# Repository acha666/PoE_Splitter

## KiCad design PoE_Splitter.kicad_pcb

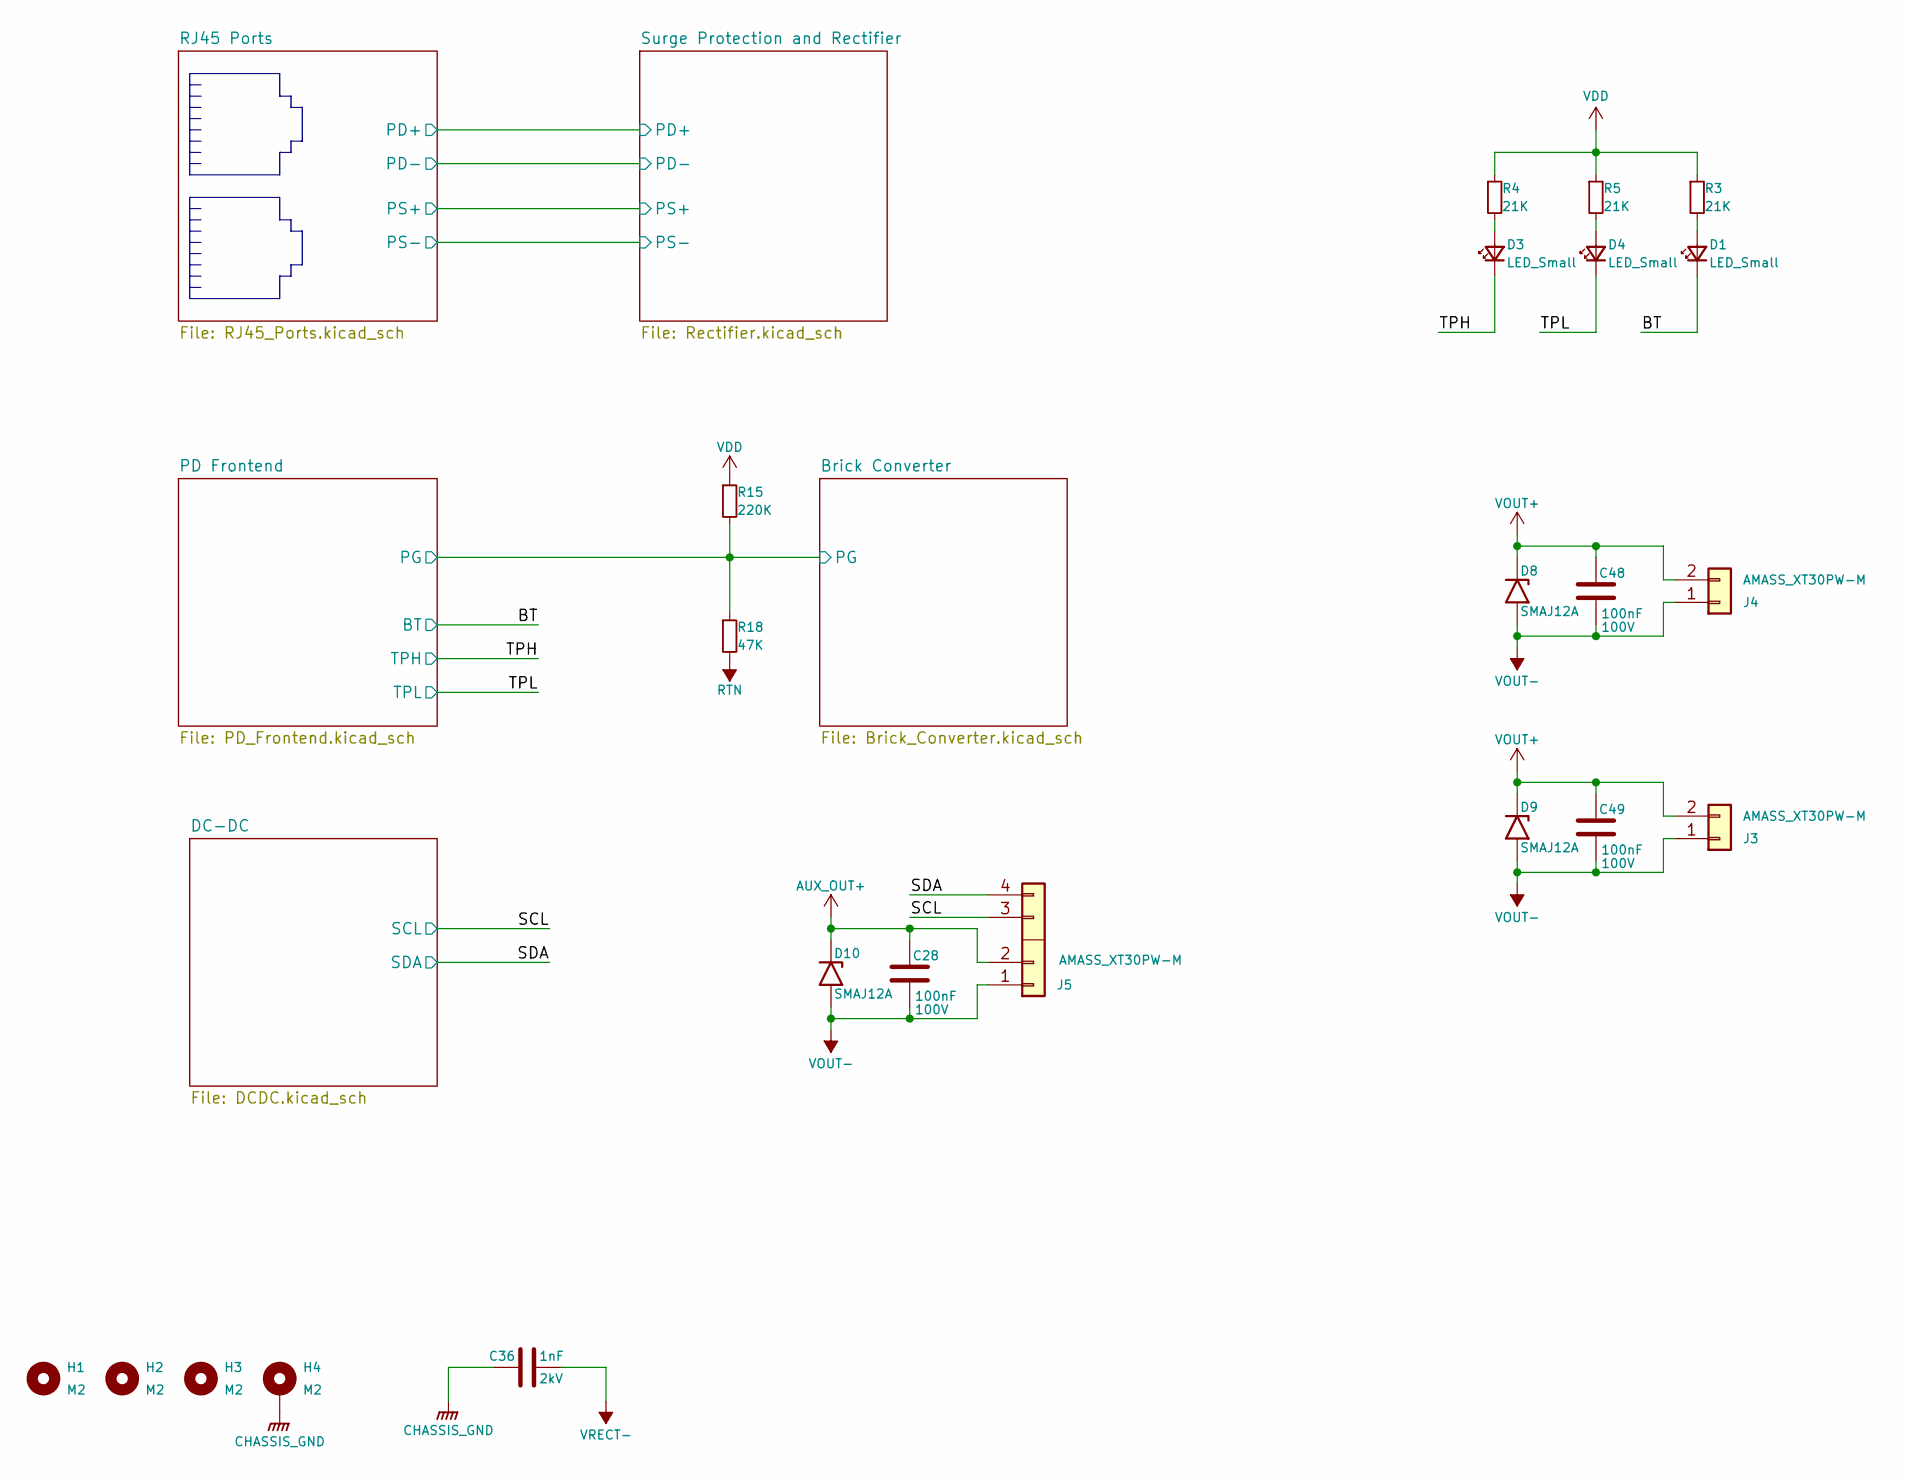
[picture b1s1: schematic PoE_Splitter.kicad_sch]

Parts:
C28: 100nF; C_0805_2012Metric; Rated Voltage 100V
C36: 1nF; C_1808_4520Metric; Rated Voltage 2kV
C48, C49: 100nF; C_1812_4532Metric; Rated Voltage 100V
D1, D3, D4: LED_Small; LED_0603_1608Metric
D8, D9, D10: SMAJ12A; D_SMA
H1, H2, H3: M2; MountingHole_2.2mm_M2_ISO7380
H4: M2; MountingHole_2.2mm_M2_ISO7380_Pad
J3, J4: AMASS_XT30PW-M; AMASS_XT30PW-M_1x02_P2.50mm_Horizontal
J5: AMASS_XT30PW-M; AMASS_XT30PW(2+2)-M_Horizontal
R3, R4, R5: 21K; R_0603_1608Metric
R15: 220K; R_0603_1608Metric
R18: 47K; R_0603_1608Metric

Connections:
/BT: D1.1 (K); also elsewhere on the board
/Brick Converter/PG: R15.2, R18.1; also elsewhere on the board
/SCL: J5.3 (Pin_1); also elsewhere on the board
/SDA: J5.4 (Pin_2); also elsewhere on the board
/TPH: D3.1 (K); also elsewhere on the board
/TPL: D4.1 (K); also elsewhere on the board
AUX_OUT+: C28.1, D10.1 (A1), J5.2; also elsewhere on the board
CHASSIS_GND: C36.1, H4.1 (1_1); also elsewhere on the board
unnamed: D1.2 (A), R3.2
unnamed: D3.2 (A), R4.2
unnamed: D4.2 (A), R5.2
RTN: R18.2; also elsewhere on the board
VDD: R3.1, R4.1, R5.1, R15.1; also elsewhere on the board
VOUT+: C48.1, C49.1, D8.1 (A1), D9.1 (A1), J3.2, J4.2; also elsewhere on the board
VOUT-: C28.2, C48.2, C49.2, D8.2 (A2), D9.2 (A2), D10.2 (A2), J3.1, J4.1, J5.1; also elsewhere on the board
VRECT-: C36.2; also elsewhere on the board

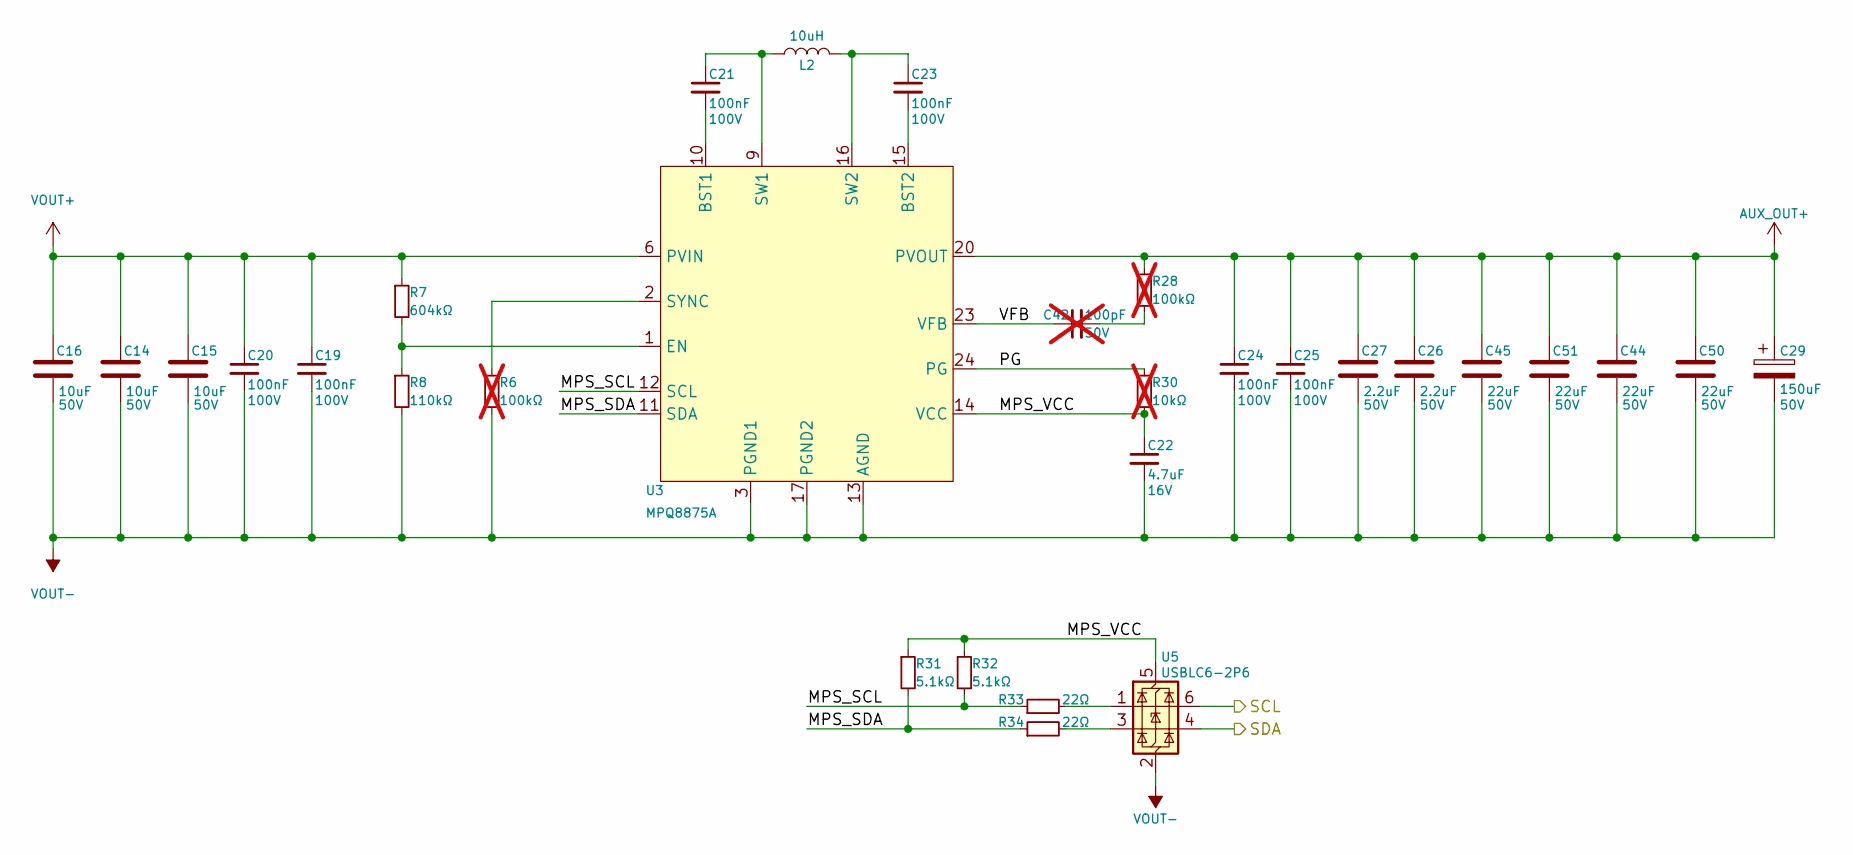
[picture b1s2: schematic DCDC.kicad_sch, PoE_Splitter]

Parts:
C14, C15, C16: 10uF; C_0805_2012Metric; Rated Voltage 50V
C19, C20, C21, C23, C24, C25: 100nF; C_0603_1608Metric; Rated Voltage 100V
C22: 4.7uF; C_0603_1608Metric; Rated Voltage 16V
C26, C27: 2.2uF; C_0805_2012Metric; Rated Voltage 50V
C29: 150uF; CP_Elec_6.3x7.7; Rated Voltage 50V
C42: 100pF; C_0603_1608Metric; Rated Voltage 50V; not fitted
C44, C45, C50, C51: 22uF; C_1206_3216Metric; Rated Voltage 50V
L2: 10uH; L_Chilisin_BWVS00808040
R6, R28: 100kΩ; R_0603_1608Metric; not fitted
R7: 604kΩ; R_0603_1608Metric
R8: 110kΩ; R_0603_1608Metric
R30: 10kΩ; R_0603_1608Metric; not fitted
R31, R32: 5.1kΩ; R_0603_1608Metric
R33, R34: 22Ω; R_0603_1608Metric
U3: MPQ8875A; MPS_QFN-34_4x5mm_MPQ8875A
U5: USBLC6-2P6; SOT-666

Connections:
/DC-DC/MPS_SCL: R32.2, R33.1, U3.12 (SCL)
/DC-DC/MPS_SDA: R31.2, R34.1, U3.11 (SDA)
/DC-DC/MPS_VCC: C22.1, R30.2, R31.1, R32.1, U3.14 (VCC), U5.5 (VBUS)
/DC-DC/PG: R30.1, U3.24 (PG)
/DC-DC/VFB: C42.1, U3.23 (VFB)
/SCL: U5.6 (I/O1); also elsewhere on the board
/SDA: U5.4 (I/O2); also elsewhere on the board
AUX_OUT+: C24.1, C25.1, C26.1, C27.1, C29.1, C44.1, C45.1, C50.1, C51.1, R28.1, U3.20 (PVOUT), U3.21 (PVOUT), U3.22 (PVOUT); also elsewhere on the board
unnamed: C21.1, L2.1, U3.9 (SW1), U3.28 (SW1), U3.29 (SW1), U3.30 (SW1)
unnamed: C23.1, L2.2, U3.16 (SW2), U3.25 (SW2), U3.31 (SW2), U3.32 (SW2)
unnamed: C42.2, R28.2
unnamed: R33.2, U5.1 (I/O1)
unnamed: R34.2, U5.3 (I/O2)
unnamed: C21.2, U3.10 (BST1)
unnamed: C23.2, U3.15 (BST2)
unnamed: R7.2, R8.1, U3.1 (EN)
unnamed: R6.1, U3.2 (SYNC)
VOUT+: C14.1, C15.1, C16.1, C19.1, C20.1, R7.1, U3.6 (PVIN), U3.7 (PVIN), U3.8 (PVIN), U3.27 (PVIN), U3.34 (PVIN); also elsewhere on the board
VOUT-: C14.2, C15.2, C16.2, C19.2, C20.2, C22.2, C24.2, C25.2, C26.2, C27.2, C29.2, C44.2, C45.2, C50.2, C51.2, R6.2, R8.2, U3.3 (PGND1), U3.4 (PGND1), U3.5 (PGND1), U3.13 (AGND), U3.17 (PGND2), U3.18 (PGND2), U3.19 (PGND2), U3.26 (PGND2), U3.33 (PGND2), U5.2 (GND); also elsewhere on the board

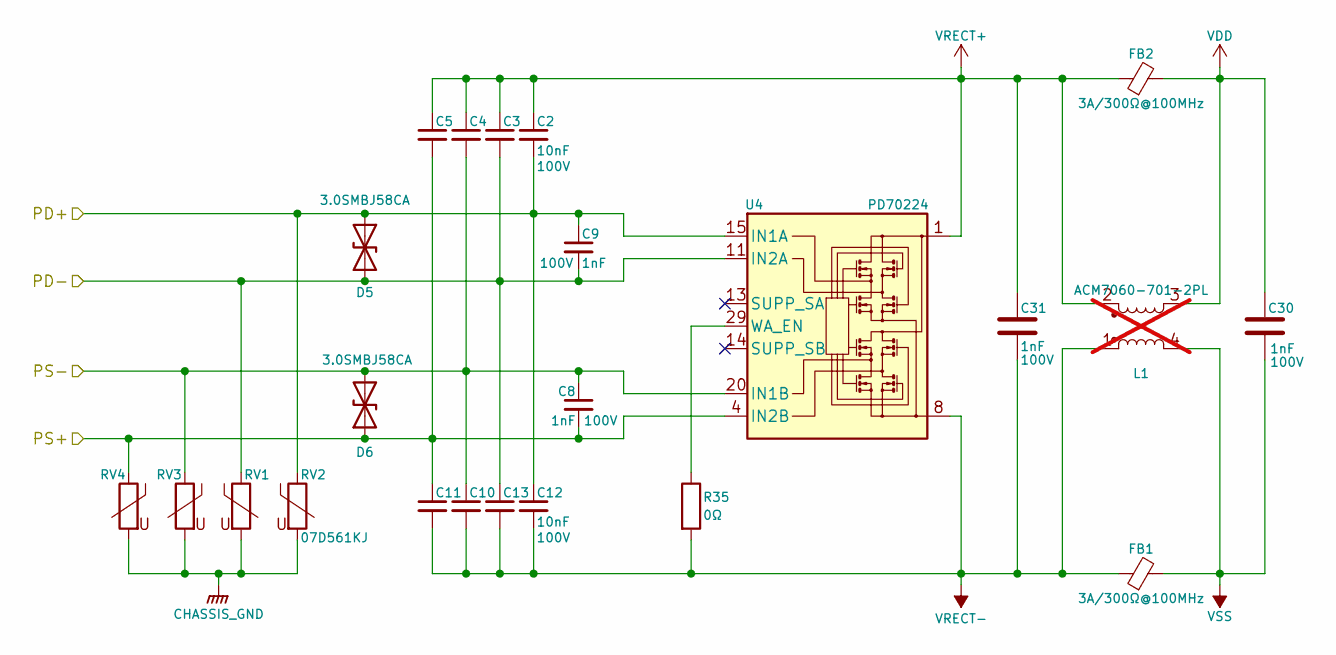
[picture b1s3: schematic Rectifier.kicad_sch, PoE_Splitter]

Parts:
C2, C3, C4, C5, C10, C11, C12, C13: 10nF; C_0603_1608Metric; Rated Voltage 100V
C8, C9: 1nF; C_0603_1608Metric; Rated Voltage 100V
C30, C31: 1nF; C_1206_3216Metric; Rated Voltage 100V
D5, D6: 3.0SMBJ58CA; D_SMB
FB1, FB2: 3A/300Ω@100MHz; L_0805_2012Metric
L1: ACM7060-701-2PL; L_CommonModeChoke_TDK_ACM7060; not fitted
R35: 0Ω; R_1206_3216Metric
RV1, RV2, RV3, RV4: 07D561KJ; RV_Disc_D9mm_W4mm_P5mm
U4: PD70224; Microsemi_QFN-40-32-2EP_6x8mm_P0.5mm

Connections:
/RJ45 Ports/PD+: C2.2, C9.1, C12.1, D5.1 (A1), RV2.1, U4.15 (IN1A), U4.16 (IN1A), U4.27 (IN1A), U4.28 (IN1A); also elsewhere on the board
/RJ45 Ports/PD-: C3.2, C9.2, C13.1, D5.2 (A2), RV1.1, U4.11 (IN2A), U4.12 (IN2A), U4.31 (IN2A), U4.32 (IN2A); also elsewhere on the board
/RJ45 Ports/PS+: C5.2, C8.2, C11.1, D6.1 (A1), RV4.1, U4.4 (IN2B), U4.5 (IN2B), U4.6 (IN2B), U4.7 (IN2B); also elsewhere on the board
/RJ45 Ports/PS-: C4.2, C8.1, C10.1, D6.2 (A2), RV3.1, U4.20 (IN1B), U4.21 (IN1B), U4.22 (IN1B), U4.23 (IN1B); also elsewhere on the board
CHASSIS_GND: RV1.2, RV2.2, RV3.2, RV4.2; also elsewhere on the board
unnamed: R35.1, U4.29 (WA_EN)
VDD: C30.1, FB2.2, L1.3; also elsewhere on the board
VRECT+: C2.1, C3.1, C4.1, C5.1, C31.1, FB2.1, L1.2, U4.1, U4.2, U4.3, U4.24, U4.25, U4.26, U4.33
VRECT-: C10.2, C11.2, C12.2, C13.2, C31.2, FB1.1, L1.1, R35.2, U4.8, U4.9, U4.10, U4.17, U4.18, U4.19, U4.34; also elsewhere on the board
VSS: C30.2, FB1.2, L1.4; also elsewhere on the board

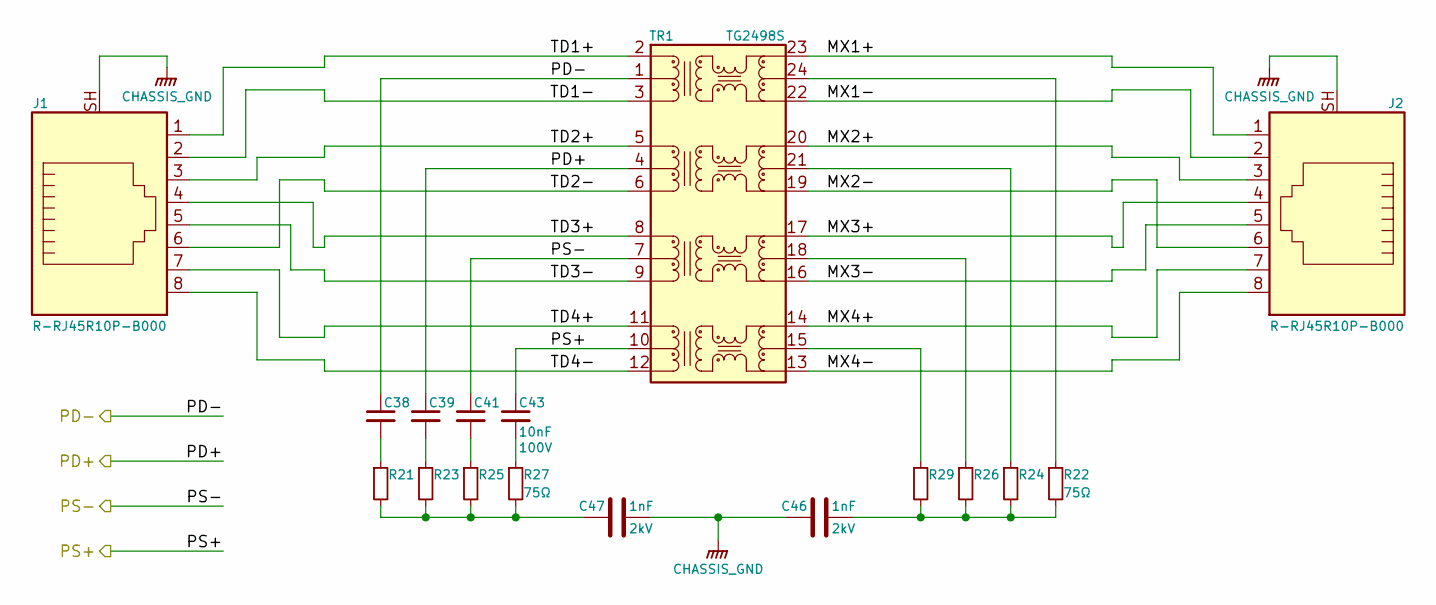
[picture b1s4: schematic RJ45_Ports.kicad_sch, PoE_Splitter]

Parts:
C38, C39, C41, C43: 10nF; C_0603_1608Metric; Rated Voltage 100V
C46, C47: 1nF; C_1808_4520Metric; Rated Voltage 2kV
J1, J2: R-RJ45R10P-B000; RJ45_Ckmtw_R-RJ45R10P-B000
R21, R22, R23, R24, R25, R26, R27, R29: 75Ω; R_0603_1608Metric
TR1: TG2498S; Transformer_Ethernet_CNDTek_TG2498S

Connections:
/RJ45 Ports/MX1+: J2.1, TR1.23 (MX1+)
/RJ45 Ports/MX1-: J2.2, TR1.22 (MX1-)
/RJ45 Ports/MX2+: J2.3, TR1.20 (MX2+)
/RJ45 Ports/MX2-: J2.6, TR1.19 (MX2-)
/RJ45 Ports/MX3+: J2.4, TR1.17 (MX3+)
/RJ45 Ports/MX3-: J2.5, TR1.16 (MX3-)
/RJ45 Ports/MX4+: J2.7, TR1.14 (MX4+)
/RJ45 Ports/MX4-: J2.8, TR1.13 (MX4-)
/RJ45 Ports/PD+: C39.1, TR1.4 (TCT2); also elsewhere on the board
/RJ45 Ports/PD-: C38.1, TR1.1 (TCT1); also elsewhere on the board
/RJ45 Ports/PS+: C43.1, TR1.10 (TCT4); also elsewhere on the board
/RJ45 Ports/PS-: C41.1, TR1.7 (TCT3); also elsewhere on the board
/RJ45 Ports/TD1+: J1.1, TR1.2 (TD1+)
/RJ45 Ports/TD1-: J1.2, TR1.3 (TD1-)
/RJ45 Ports/TD2+: J1.3, TR1.5 (TD2+)
/RJ45 Ports/TD2-: J1.6, TR1.6 (TD2-)
/RJ45 Ports/TD3+: J1.4, TR1.8 (TD3+)
/RJ45 Ports/TD3-: J1.5, TR1.9 (TD3-)
/RJ45 Ports/TD4+: J1.7, TR1.11 (TD4+)
/RJ45 Ports/TD4-: J1.8, TR1.12 (TD4-)
CHASSIS_GND: C46.1, C47.2, J1.SH, J2.SH; also elsewhere on the board
unnamed: C38.2, R21.1
unnamed: C39.2, R23.1
unnamed: C41.2, R25.1
unnamed: C43.2, R27.1
unnamed: C46.2, R22.2, R24.2, R26.2, R29.2
unnamed: C47.1, R21.2, R23.2, R25.2, R27.2
unnamed: R22.1, TR1.24 (MCT1)
unnamed: R24.1, TR1.21 (MCT2)
unnamed: R26.1, TR1.18 (MCT3)
unnamed: R29.1, TR1.15 (MCT4)

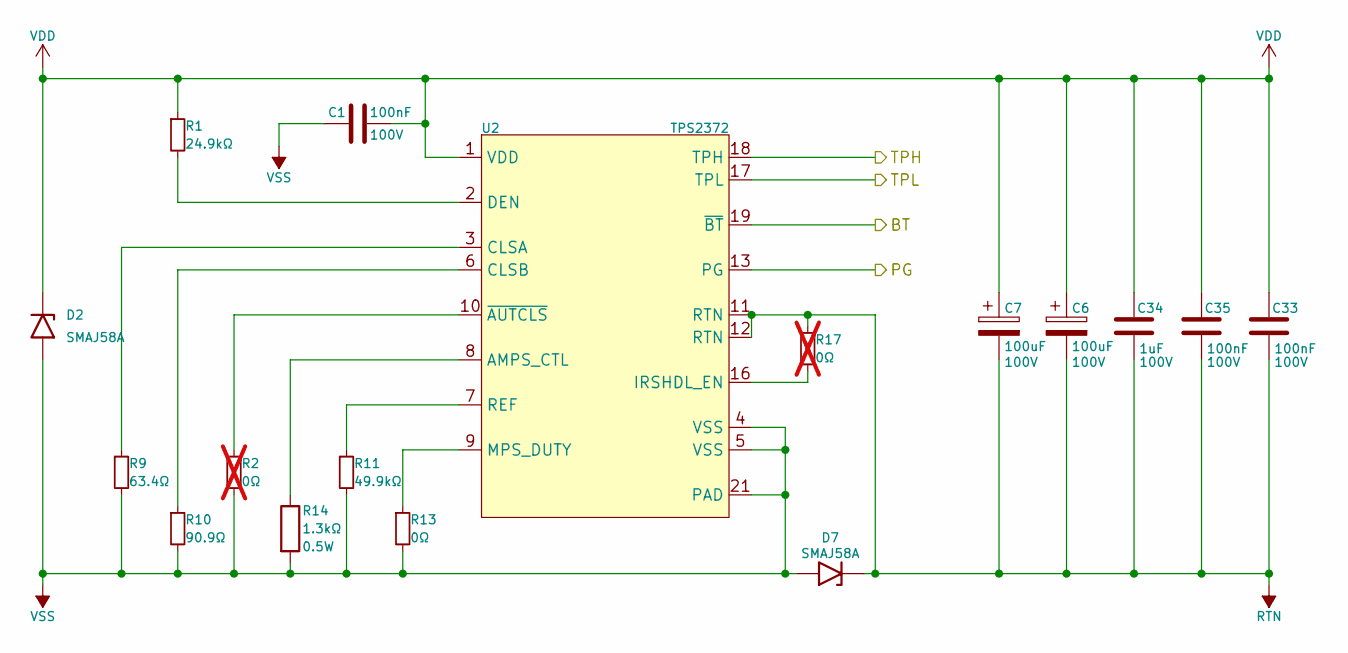
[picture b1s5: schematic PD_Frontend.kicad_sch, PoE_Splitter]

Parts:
C1: 100nF; C_0603_1608Metric; Rated Voltage 100V
C6, C7: 100uF; CP_Radial_D10.0mm_P5.00mm; Rated Voltage 100V
C33, C35: 100nF; C_1812_4532Metric; Rated Voltage 100V
C34: 1uF; C_1812_4532Metric; Rated Voltage 100V
D2, D7: SMAJ58A; D_SMA
R1: 24.9kΩ; R_0603_1608Metric
R2, R17: 0Ω; R_0603_1608Metric; not fitted
R9: 63.4Ω; R_0603_1608Metric
R10: 90.9Ω; R_0603_1608Metric
R11: 49.9kΩ; R_0603_1608Metric
R13: 0Ω; R_0603_1608Metric
R14: 1.3kΩ; R_0805_2012Metric
U2: TPS2372; Texas_RGW0020A_VQFN-20-1EP_5x5mm_P0.65mm_EP3.15x3.15mm

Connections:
/BT: U2.19 (~BT); also elsewhere on the board
/Brick Converter/PG: U2.13 (PG); also elsewhere on the board
/TPH: U2.18 (TPH); also elsewhere on the board
/TPL: U2.17 (TPL); also elsewhere on the board
unnamed: R14.1, U2.8 (AMPS_CTL)
unnamed: R9.1, U2.3 (CLSA)
unnamed: R10.1, U2.6 (CLSB)
unnamed: R1.2, U2.2 (DEN)
unnamed: R17.2, U2.16 (IRSHDL_EN)
unnamed: R13.1, U2.9 (MPS_DUTY)
unnamed: R11.1, U2.7 (REF)
unnamed: R2.1, U2.10 (~AUTCLS)
RTN: C6.2, C7.2, C33.2, C34.2, C35.2, D7.1 (A1), R17.1, U2.11 (RTN), U2.12 (RTN); also elsewhere on the board
VDD: C1.2, C6.1, C7.1, C33.1, C34.1, C35.1, D2.1 (A1), R1.1, U2.1 (VDD); also elsewhere on the board
VSS: C1.1, D2.2 (A2), D7.2 (A2), R2.2, R9.2, R10.2, R11.2, R13.2, R14.2, U2.4 (VSS), U2.5 (VSS), U2.21 (PAD); also elsewhere on the board

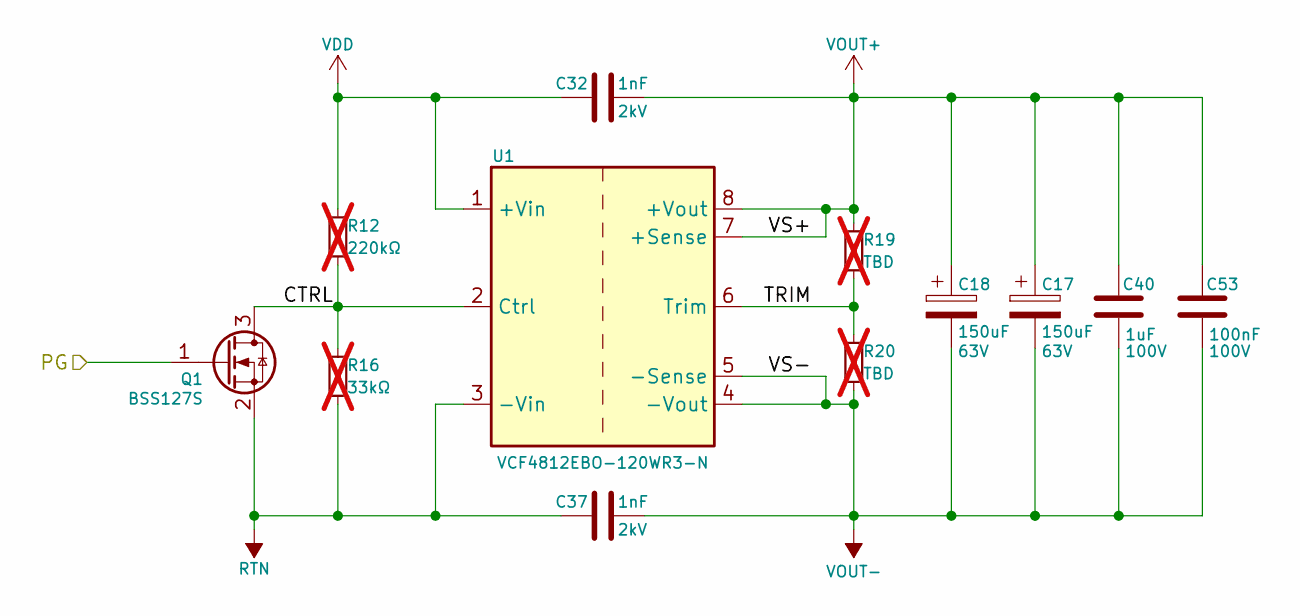
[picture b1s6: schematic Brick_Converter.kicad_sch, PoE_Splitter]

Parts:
C17, C18: 150uF; CP_Radial_D10.0mm_P5.00mm; Rated Voltage 63V
C32, C37: 1nF; C_1812_4532Metric; Rated Voltage 2kV
C40: 1uF; C_1812_4532Metric; Rated Voltage 100V
C53: 100nF; C_1812_4532Metric; Rated Voltage 100V
Q1: BSS127S; SOT-23
R12: 220kΩ; R_0603_1608Metric; not fitted
R16: 33kΩ; R_0603_1608Metric; not fitted
R19, R20: TBD; R_0603_1608Metric; not fitted
U1: VCF4812EBO-120WR3-N; Converter_DCDC_Eighth_Brick

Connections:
/Brick Converter/CTRL: Q1.3 (D), R12.2, R16.1, U1.2 (Ctrl)
/Brick Converter/PG: Q1.1 (G); also elsewhere on the board
/Brick Converter/TRIM: R19.2, R20.1, U1.6 (Trim)
RTN: C37.1, Q1.2 (S), R16.2, U1.3 (-Vin); also elsewhere on the board
VDD: C32.1, R12.1, U1.1 (+Vin); also elsewhere on the board
VOUT+: C17.1, C18.1, C32.2, C40.1, C53.1, R19.1, U1.7 (+Sense), U1.8 (+Vout); also elsewhere on the board
VOUT-: C17.2, C18.2, C37.2, C40.2, C53.2, R20.2, U1.4 (-Vout), U1.5 (-Sense); also elsewhere on the board

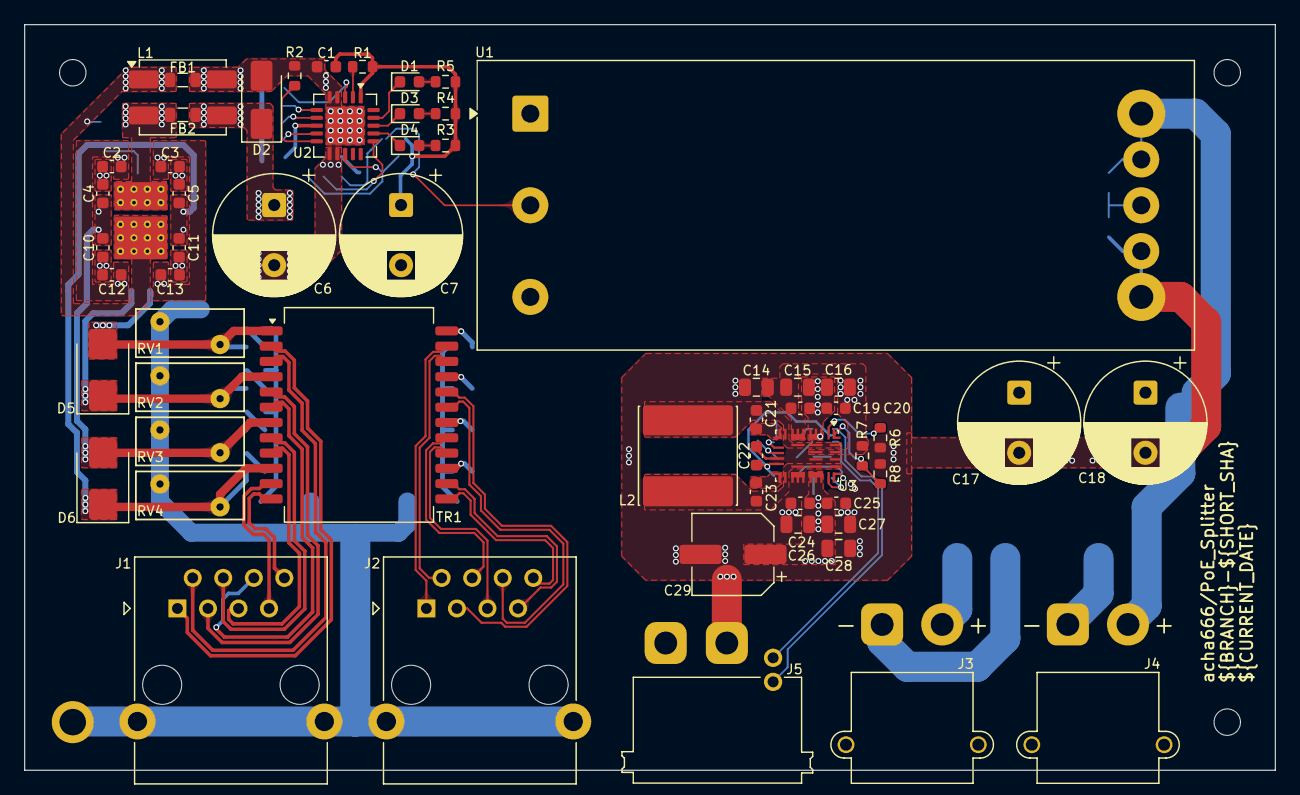
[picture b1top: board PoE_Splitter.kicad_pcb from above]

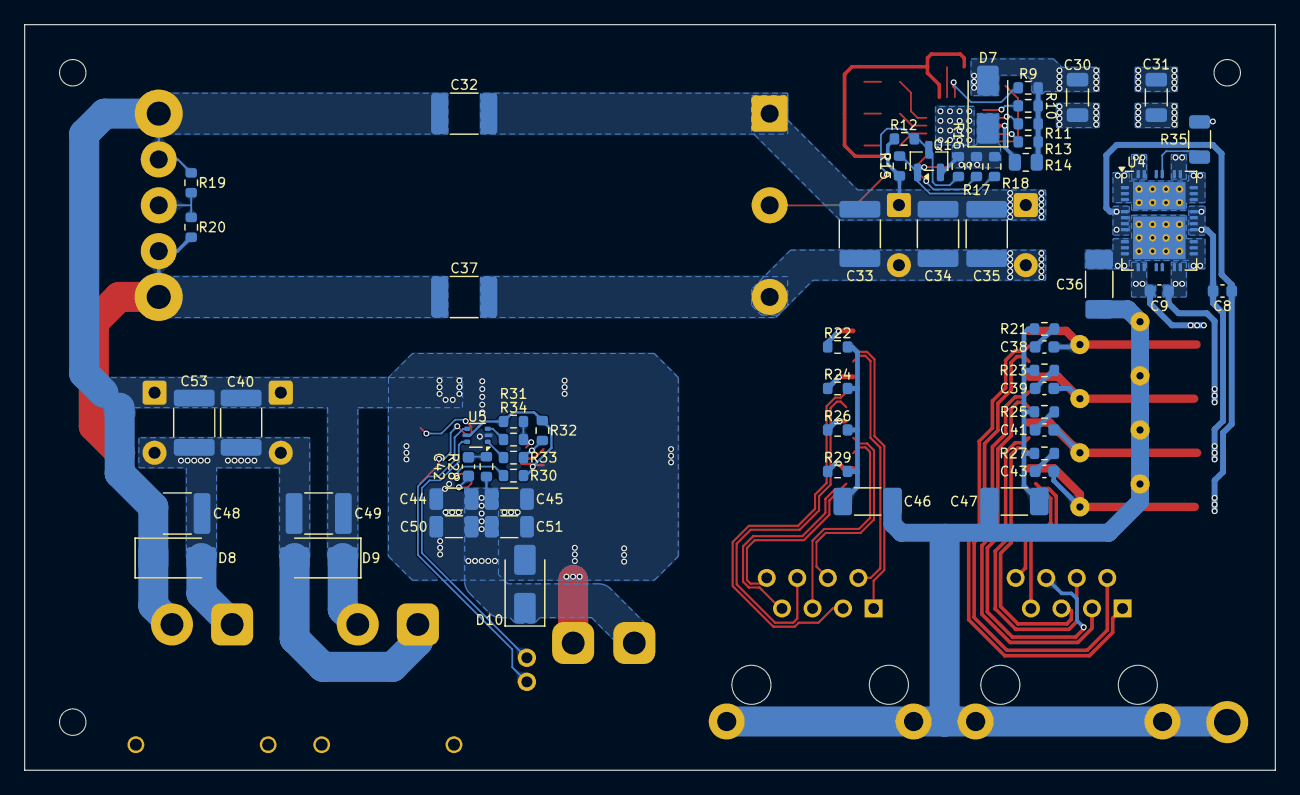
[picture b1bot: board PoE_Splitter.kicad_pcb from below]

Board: 2 copper layers, 104.0 x 62.0 mm, 121 parts (59 on the bottom side), 73 nets.

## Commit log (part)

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2026-06-28 Init
2026-06-28 Add GPL v3 license
2026-06-30 add ci
2026-06-30 include dev branch in CI
2026-06-30 fix drc exclusions
2026-06-30 reduce POWER netclass clearance
2026-06-30 fix 3d model ref
2026-06-30 add desc text
2026-06-30 add sheet titles
2026-06-30 MPQ boost cap value MPQ PG pull-up res all res value unit naming
2026-06-30 refresh teardrops

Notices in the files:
Brick_Converter.kicad_sch:
GPL-3.0 Licensed
